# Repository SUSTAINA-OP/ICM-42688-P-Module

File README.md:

<html lang="en">
  <head>
    <meta charset="uft-8">
    <meta name="author" content="Masato Kubotera">
  </head>
  <body>
    <strong>This product is currently under development and has not been tested.</strong>
    <h1>ICM-42688-P-Module</h1>
    <h2>About ICM-42688-P-Module</h2>
    <p>
      ICM-42688-P-Module is a module of 6-axis acceleration/gyro sensor "<a href="https://product.tdk.com/en/search/sensor/mortion-inertial/imu/info?part_no=ICM-42688-P">ICM-42688-P</a>" made by TDK.
    </p>
    <h2>Features of Ver. 1.0</h2>
    <h3>PCB</h3>
        <ul>
            <li>4" x 5" (10.16 mm x 12.70 mm) PCB layout</li>
            <li>2 x 5-pin + 1-pin 0.1" spaced PTH
                <ul>
                    <li><strong>VDD</strong> : Power supply voltage</li>
                    <li><strong>VDDIO</strong> : IO power supply voltage</li>
                    <li><strong>SCL / SCLK</strong> : I2C serial clock / AP SPI serial clock</li>
                    <li><strong>SDA / SDI</strong> :  I2C serial data / SPI serial data input (4-wire mode)</li>
                    <li><strong>AD0 / SDO</strong> :  I2C slave address LSB / SPI serial data output (4-wire mode)</li>
                    <li><strong>CS</strong> : SPI Chip select (Connect to VDDIO if using I2C interface)</li>
                    <li><strong>INT1 / INT</strong> : Interrupt 1 / All interrupts mapped to pin 4</li>
                    <li><strong>INT2 / FSYNC / CLKIN</strong> : Interrupt 2 / Frame sync input / External clock input</li>
                    <li><strong>GND</strong> : Common Ground</li>
                    <li><strong>NC</strong> : Non Connection</li>
                </ul>
            </li>
        </ul>
        
    <h3><a href="https://product.tdk.com/en/search/sensor/mortion-inertial/imu/info?part_no=ICM-42688-P">ICM-42688-P</a></h3>
        <ul>
            <li>Input Voltage Range: 1.71V to 3.6V</li>
            <li>Digital-output X-, Y-, and Z-axis angular rate sensors (gyroscopes) with programmable full-scale range of ±15.625, ±31.25,±62.5, ±125, ±250, ±500, ±1000, and ±2000 degrees/sec</li>
            <li>Digital-output X-, Y-, and Z-axis accelerometer with programmable full-scale range of ±2g, ±4g ±8g and ±16g</li>
            <li>The host interface can be configured to support I3CSM slave, I2C slave, or SPI slave modes. The I3CSM interface supports speeds up to 12.5MHz (data rates up to 12.5Mbps in SDR mode, 25Mbps in DDR mode), the I2C interface supports speeds up to 1 MHz, and the SPI interface supports speeds up to 24 MHz.</li>
            <li>Digital-output temperature sensor</li>
            <li>I2C Address: 0x68 (AD0=0), 0x69 (AD0=1)</li>
        </ul>
    <h2>Repository Contents</h2>
        
        <dl>
            <dt>
                <a href="/images">\images</a>
            </dt>
            <dd>PCB preview images and capture of design screen</dd>
            <dt>
                <a href="/libraries">\libraries</a>
            </dt>
            <dd>Libraries used in Autodesk Eagle design</dd>
            <dt>
                <a href="/Schematic.pdf">Schematic.pdf</a>
            </dt>
            <dd>Circuit diagram of the product</dd>
            <dt>
                <a href="/BOM.txt">BOM.txt</a>
            </dt>
            <dd>Parts lists output from design file</dd>
            <dt>*.brd</dt>
            <dd>Board wiring design file by Autodesk Eagle</dd>
            <dt>*.sch</dt>
            <dd>Circuit diagram design file by Autodesk Eagle</dd>
            <dt>
                <a href="/Gerber_data.zip">\Gerber_data.zip</a>
            </dt>
            <dd>Zip folder of Gerber format files for PCB manufacturing</dd>
            <dt>
                <a href="/LICENSE">LICENSE</a>
            </dt>
            <dd>License to use the product</dd>
            <dt>
                <a href="/.gitignore">.gitignore</a>
            </dt>
            <dd>File to exclude cache files from management</dd>
        </dl>
    </p>
    <h2>Documentation</h2>
      <p>
        <h3>BOM</h3>
          <table>
            <thead>
              <tr>
                <th> Eagle Design Parts # </th>
                <th> Q'ty </th>
                <th> Mfr. Product # </th>
                <th> Supplier </th>
                <th> Description </th>
              </tr>
            </thead>
            <tbody>
              <tr>
                <td>U1</td>
                <td>1</td>
                <td>ICM-42688-P</td>
                <td><a href="https://www.mouser.jp/ProductDetail/410-ICM-42688-P">Mouser</a></td>
                <td>Inertial Measurement Units 6-axis</td>
              </tr>
              <tr>
                <td>C1</td>
                <td>1</td>
                <td>GRM155R71C104JA88D</td>
                <td><a href="https://www.mouser.jp/ProductDetail/81-GRM155R71C104JA8D">Mouser</a></td>
                <td>Multilayer Ceramic Capacitor SMD 0.1uF 16V 5% X7R 0402</td>
              </tr>
              <tr>
                <td>C2</td>
                <td>1</td>
                <td>GRM155Z71A225KE01D</td>
                <td><a href="https://www.mouser.jp/ProductDetail/81-GRM155Z71A225KE1D">Mouser</a></td>
                <td>Multilayer Ceramic Capacitor SMD 2.2uF 10V 10% X7R 0402</td>
              </tr>
              <tr>
                <td>C3</td>
                <td>1</td>
                <td>GRM155R71E103KA01D</td>
                <td><a href="https://www.mouser.jp/ProductDetail/81-GRM36X103K25">Mouser</a></td>
                <td>Multilayer Ceramic Capacitor SMD 10nF 25V 10% X7R 0402</td>
              </tr>
            </tbody>
          </table>
          Exterior components were determined with reference to <a href="https://product.tdk.com/system/files/dam/doc/product/sensor/mortion-inertial/imu/data_sheet/ds-000347-icm-42688-p-v1.6.pdf#page=22">ICM-42688-P Datasheet</a>.
      </p>
    <h2>Confirmation of operation</h2>
    <p>
      The following Arduino Library https://github.com/finani/ICM42688 was used to verify the operation.<br>      
      The Arduino Board used is "<a href="https://docs.arduino.cc/hardware/due">Arduino Due</a>".<br>
      Up to 3.6V is the supply voltage for VDD and VDDIO of this module. 
      <ul>
        <li><strong>SPI</strong> : https://github.com/finani/ICM42688/tree/master/examples/Basic_SPI</li>
        Wiring with Arudino Due is done as follows.
        <table>
            <thead>
              <tr>
                <th> ICM-42688-P Module Pin </th>
                <th> Arudiono Board Pin </th>
              </tr>
            </thead>
            <tbody>
              <tr>
                <td>VDD</td>
                <td>3.3V</td>
              </tr>
              <tr>
                <td>VDDIO</td>
                <td>3.3V</td>
              </tr>
              <tr>
                <td>SCL/SCLK</td>
                <td>SCK</td>
              </tr>
              <tr>
                <td>SDA _SDI</td>
                <td>MOSI</td>
              </tr>
              <tr>
                <td>AD0/SD0</td>
                <td>MISO</td>
              </tr>
              <tr>
                <td>CS</td>
                <td>Any GPIO<br>(In the case of the sample sketch, digital pin 10 of arduino due board is used .)</td>
              </tr>
              <tr>
                <td>INT1/INT</td>
                <td>-</td>
              </tr>
              <tr>
                <td>GND</td>
                <td>GND</td>
              </tr>
              <tr>
                <td>INT2/FSYNC/CLKIN</td>
                <td>-</td>
              </tr>
            </tbody>
          </table>
        <li><strong>I2C</strong> : https://github.com/finani/ICM42688/blob/master/examples/Basic_I2C/Basic_I2C.ino</li>
        4.7 kOhm resistors should be used as pullups on SDA and SCL, these resistors should pullup with a 3.3V source.<br>
        Wiring with Arudino Due is done as follows.
        <table>
            <thead>
              <tr>
                <th> ICM-42688-P Module Pin </th>
                <th> Arudiono Board Pin </th>
              </tr>
            </thead>
            <tbody>
              <tr>
                <td>VDD</td>
                <td>3.3V</td>
              </tr>
              <tr>
                <td>VDDIO</td>
                <td>3.3V</td>
              </tr>
              <tr>
                <td>SCL/SCLK</td>
                <td>SCL (digital pin 21 of arduino due board)</td>
              </tr>
              <tr>
                <td>SDA _SDI</td>
                <td>SDA (digital pin 20 of arduino due board)</td>
              </tr>
              <tr>
                <td>AD0/SD0</td>
                <td>GND for I2C address 0x68 or 3.3V for I2C address 0x69</td>
              </tr>
              <tr>
                <td>CS</td>
                <td>3.3V</td>
              </tr>
              <tr>
                <td>INT1/INT</td>
                <td>-</td>
              </tr>
              <tr>
                <td>GND</td>
                <td>GND</td>
              </tr>
              <tr>
                <td>INT2/FSYNC/CLKIN</td>
                <td>-</td>
              </tr>
            </tbody>
          </table>
      </ul>  
    </p>
    <h2>Contact</h2>
    <p>
    If you have any questions, please contact MasatoKubotera, the product's designer, by E-mail.<br>
    E-mail : <a href="mailto:masatokubotera06@yahoo.co.jp">masatokubotera06@yahoo.co.jp</a>
    </p>
    <h2>License Information</h2>
    <p>
      This product is open source.<br>
      Please review the <a href="/LICENSE">LICENSE file</a> for license information.<br>
      <br>
      <strong>ICM-42688-P-Module</strong> by Masato Kubotera is licensed under a <a href="http://creativecommons.org/licenses/by-nc-sa/4.0/">Creative Commons Attribution-NonCommercial-ShareAlike 4.0 International License</a>.
    </p>    
  </body>
</html>

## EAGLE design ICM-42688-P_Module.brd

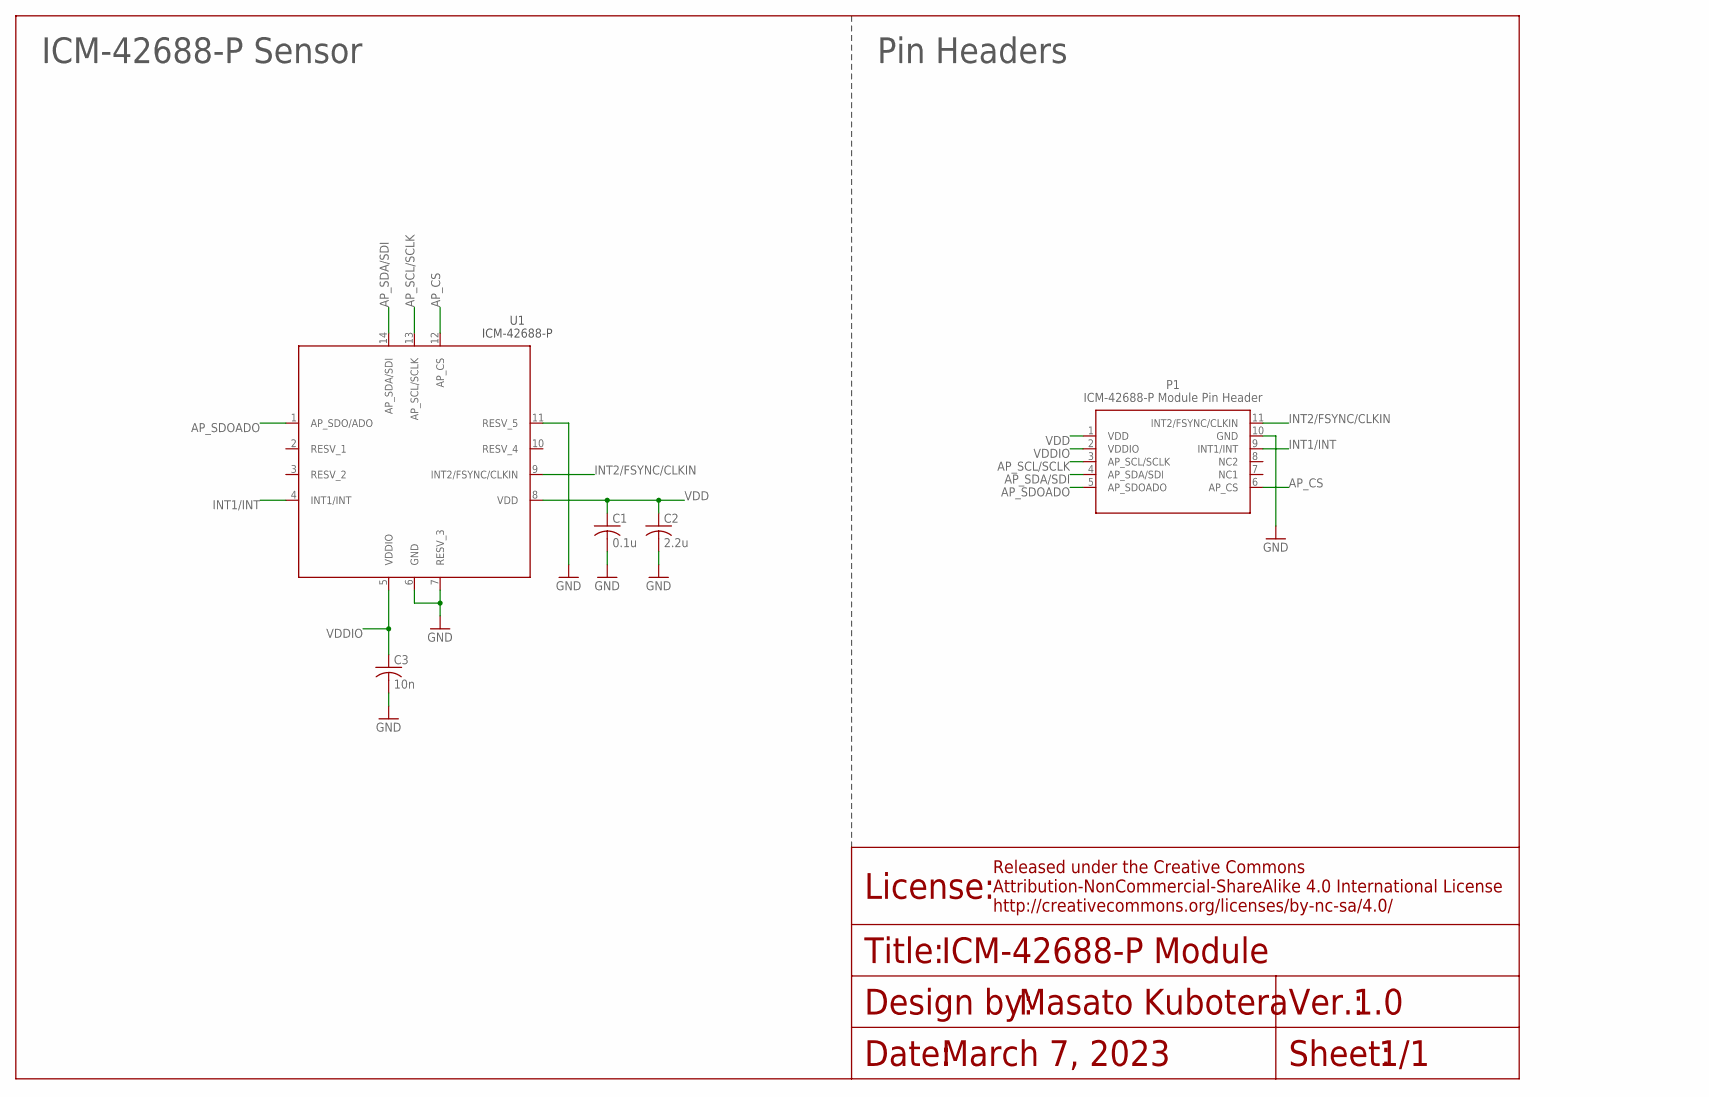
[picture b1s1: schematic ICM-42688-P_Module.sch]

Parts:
C1: 0.1u; C0402
C2: 2.2u; C0402
C3: 10n; C0402
P1: ICM-42688-P-MODULE-PINHEADER; FOR-MODULE-MAKING
U1: ICM-42688-P

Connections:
AP_CS: P1.6 (AP_CS), U1.12 (AP_CS)
AP_SCL/SCLK: P1.3 (AP_SCL/SCLK), U1.13 (AP_SCL/SCLK)
AP_SDA/SDI: P1.4 (AP_SDA/SDI), U1.14 (AP_SDA/SDI)
AP_SDOADO: P1.5 (AP_SDOADO), U1.1 (AP_SDO/ADO)
GND: C1.2, C2.2, C3.2, P1.10 (GND), U1.6 (GND), U1.7 (RESV_3), U1.11 (RESV_5)
INT1/INT: P1.9 (INT1/INT), U1.4 (INT1/INT)
INT2/FSYNC/CLKIN: P1.11 (INT2/FSYNC/CLKIN), U1.9 (INT2/FSYNC/CLKIN)
VDD: C1.1, C2.1, P1.1 (VDD), U1.8 (VDD)
VDDIO: C3.1, P1.2 (VDDIO), U1.5 (VDDIO)

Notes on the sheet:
March 7, 2023
ICM-42688-P Module
1.0
1/1
ICM-42688-P Sensor
Pin Headers

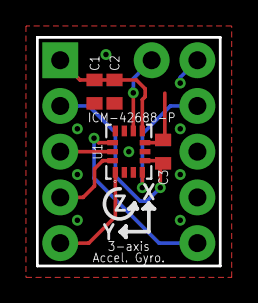
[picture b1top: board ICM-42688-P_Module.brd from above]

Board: 2 copper layers, 10.2 x 12.7 mm, 5 parts (0 on the bottom side), 9 nets.

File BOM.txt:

Qty Value                        Device                       Package           Parts Description                
1   0.1u                         C-USC0402                    C0402             C1    CAPACITOR, American symbol 
1   10n                          C-USC0402                    C0402             C3    CAPACITOR, American symbol 
1   2.2u                         C-USC0402                    C0402             C2    CAPACITOR, American symbol 
1   ICM-42688-P                  ICM-42688-P                  ICM-42688-P       U1                               
1   ICM-42688-P-MODULE-PINHEADER ICM-42688-P-MODULE-PINHEADER FOR-MODULE-MAKING P1

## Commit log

2022-10-06 Initial upload of data
2022-10-06 Fixed wrong file hierarchy
2023-03-07 Rename directory from image to images
2023-03-07 Update data for ordering
2023-03-07 add piout image
2023-03-07 Correct spelling errors in silk printing

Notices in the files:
parts and their libraries:
Frame: Released under the Creative Commons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
